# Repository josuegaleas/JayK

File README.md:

# JayK
Full-size mechanical keyboard with USB-C and no lighting, inspired by the [ONO-SENDAI MATRIX 83](https://imgur.com/a/v5pzh#FiXKcm0).

JayK Pro with *more* features can be found [here](https://github.com/josuegaleas/JayK-Pro).

### Disclaimer
I have not printed this PCB out yet, and I am not 100% certain the design works. Please print with discretion.

## Features
- TMK-based firmware
- Numpad on the left for comfort
- USB-C port for modernness
- No lighting for less complexity and lower cost

## Layout
### Default Layer

### Other Layers

JSON files for these layouts can be found [here](https://gist.github.com/josuegaleas/417a4ff5fc216ecdc7868effc9a7b36f) and [here](https://gist.github.com/josuegaleas/c81fd5085f4eeaf2fcede5950b9f7410), for editing in [KLE](http://www.keyboard-layout-editor.com/).

## Major Components
- Microcontroller — [Microchip's AT90USB1286](https://www.microchip.com/wwwproducts/en/AT90USB1286)
- USB-C Port — [Amphenol's 12401610E4#2A](https://www.amphenol-icc.com/usb-3-1-type-c-gen-2-12401610e42a.html)
- Crystal — [EPSON's FA-238](https://www5.epsondevice.com/en/products/crystal_unit/fa238.html)

## Tools
- Layout — [Keyboard Layout Editor](http://www.keyboard-layout-editor.com/)
- PCB — [KiCad EDA](https://kicad.org/)
- Firmware
	- [tmk_core](https://github.com/tmk/tmk_core)
	- [avr-gcc](https://www.gnu.org/software/gcc/gcc.html)
	- [dfu-programmer](https://dfu-programmer.sourceforge.io/)
- Models — [Plate & Case Builder](http://builder.swillkb.com/)

### KiCad Libraries
- [kicad_lib_tmk](https://github.com/tmk/kicad_lib_tmk)
- [keyboard_parts.pretty](https://github.com/tmk/keyboard_parts.pretty)
- [keebs.pretty](https://github.com/egladman/keebs.pretty)
- [jay-kicad-lib](https://github.com/josuegaleas/jay-kicad-lib)

## Development
Clone this repository with:
```bash
git clone --recursive https://github.com/josuegaleas/JayK.git
```

### Hardware
Within KiCad, navigate to the `PCB` folder and open `JayK.pro`.

Using a grid size of `0.0234375` inches for editing the layout.

### Software
Firmware can be compiled using `make` within the `Firmware` folder.

Refer to [this](https://github.com/tmk/tmk_keyboard/blob/master/tmk_core/doc/build.md) for dependencies and programming.

## References
- Layout — [Physical Keyboard Layouts Explained In Detail](https://drop.com/talk/947/physical-keyboard-layouts-explained-in-detail)
- PCB
	- [Keyboard PCB Guide](https://github.com/ruiqimao/keyboard-pcb-guide)
	- [Teensy++ 2.0 USB Development Board](https://www.pjrc.com/store/teensypp.html)
	- [Microchip's AT90USBKEY](https://www.microchip.com/DevelopmentTools/ProductDetails/AT90USBKEY2)
- Firmware
	- [TMK Keyboard Firmware Collection](https://github.com/tmk/tmk_keyboard/)
	- [How to build your very own keyboard firmware](https://deskthority.net/viewtopic.php?f=7&t=7177&start=)

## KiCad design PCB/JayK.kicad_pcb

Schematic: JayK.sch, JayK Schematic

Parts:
C_AREF1: 100n; C_0805_2012Metric_Pad1.15x1.40mm_HandSolder
C_AVCC1: 100n; C_0805_2012Metric_Pad1.15x1.40mm_HandSolder
C_CLK1, C_CLK2: 22p; C_0805_2012Metric_Pad1.15x1.40mm_HandSolder
C_UCAP1: 1u; C_0805_2012Metric_Pad1.15x1.40mm_HandSolder
C_UVCC1: 100n; C_0805_2012Metric_Pad1.15x1.40mm_HandSolder
C_VBUS1: 10u; C_0805_2012Metric_Pad1.15x1.40mm_HandSolder
C_VCC1, C_VCC2: 100n; C_0805_2012Metric_Pad1.15x1.40mm_HandSolder
R_HWB1: 1k; R_0805_2012Metric_Pad1.15x1.40mm_HandSolder
R_RST1: 47k; R_0805_2012Metric_Pad1.15x1.40mm_HandSolder
R_USB1, R_USB2: 22; R_0805_2012Metric_Pad1.15x1.40mm_HandSolder
SW1: SW_PUSH; SW_SPST_TL3342
U1: AT90USB1286-AU; TQFP-64_14x14mm_P0.8mm
Y1: 16M; Crystal_SMD_SeikoEpson_FA238-4Pin_3.2x2.5mm_HandSoldering

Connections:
/CLK_N: C_CLK2.1, U1.24, Y1.3
/CLK_P: C_CLK1.1, U1.23, Y1.1
/D_+: R_USB2.1, U1.5
/D_-: R_USB1.1, U1.4
/D_N: R_USB1.2; also elsewhere on the board
/D_P: R_USB2.2; also elsewhere on the board
/col00: U1.28; also elsewhere on the board
/col01: U1.29; also elsewhere on the board
/col02: U1.30; also elsewhere on the board
/col03: U1.31; also elsewhere on the board
/col04: U1.32; also elsewhere on the board
/col05: U1.35; also elsewhere on the board
/col06: U1.36; also elsewhere on the board
/col07: U1.37; also elsewhere on the board
/col08: U1.38; also elsewhere on the board
/col09: U1.39; also elsewhere on the board
/col10: U1.40; also elsewhere on the board
/col11: U1.41; also elsewhere on the board
/col12: U1.42; also elsewhere on the board
/col13: U1.54; also elsewhere on the board
/col14: U1.55; also elsewhere on the board
/col15: U1.56; also elsewhere on the board
/col16: U1.57; also elsewhere on the board
/col17: U1.58; also elsewhere on the board
/col18: U1.59; also elsewhere on the board
/col19: U1.60; also elsewhere on the board
/col20: U1.61; also elsewhere on the board
/row0: U1.48; also elsewhere on the board
/row1: U1.47; also elsewhere on the board
/row2: U1.46; also elsewhere on the board
/row3: U1.45; also elsewhere on the board
/row4: U1.44; also elsewhere on the board
GND: C_AREF1.2, C_AVCC1.2, C_CLK1.2, C_CLK2.2, C_UCAP1.2, C_UVCC1.2, C_VBUS1.2, C_VCC1.2, C_VCC2.2, R_HWB1.1, SW1.1, U1.6, U1.22, U1.53, U1.63, Y1.2, Y1.4; also elsewhere on the board
unnamed: C_AREF1.1, U1.62
unnamed: C_UCAP1.1, U1.7
unnamed: R_HWB1.2, U1.43
unnamed: R_RST1.1, SW1.2, U1.20
VCC: C_AVCC1.1, C_UVCC1.1, C_VBUS1.1, C_VCC1.1, C_VCC2.1, R_RST1.2, U1.3, U1.8, U1.21, U1.52, U1.64; also elsewhere on the board

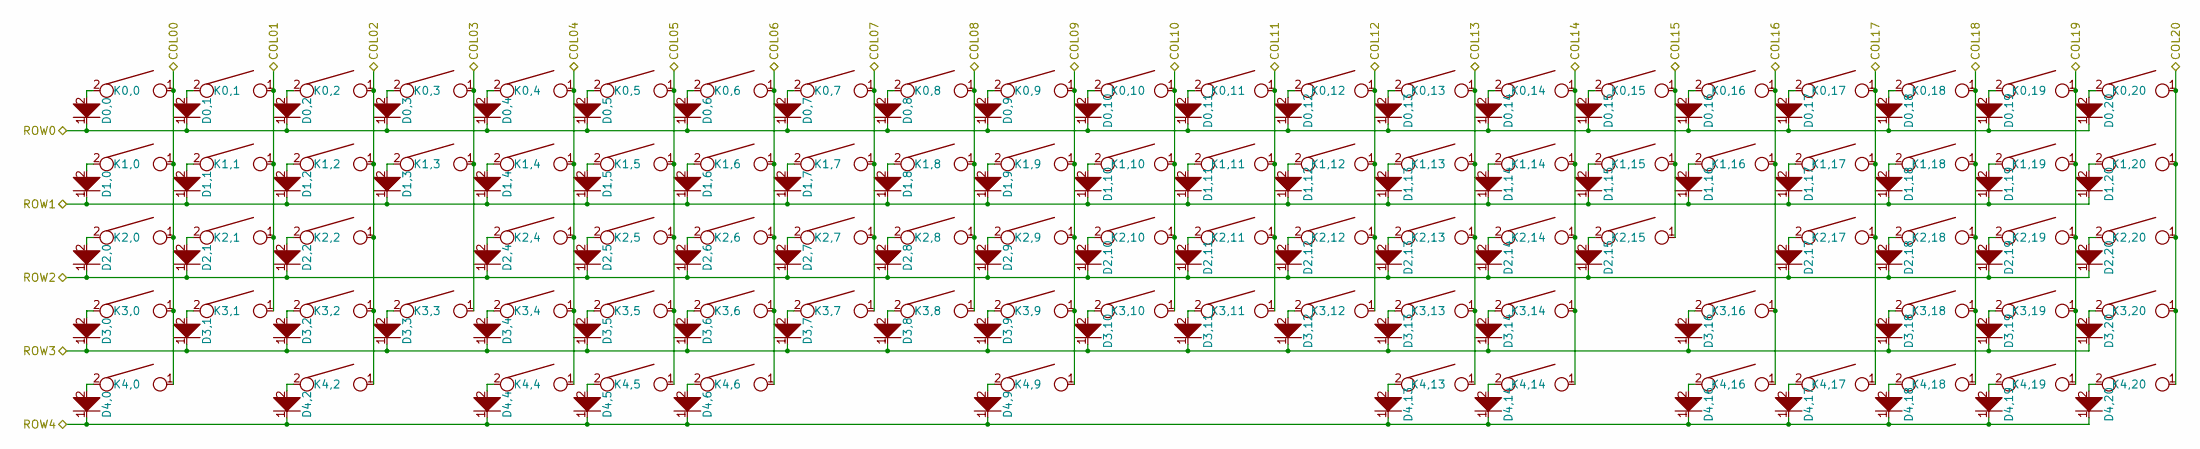
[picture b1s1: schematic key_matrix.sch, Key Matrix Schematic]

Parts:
D0,0, D0,1, D0,2, D0,3, D0,4, D0,5, D0,6, D0,7, D0,8, D0,9, D0,10, D0,11, D0,12, D0,13, D0,14, D0,15, D0,16, D0,17, D0,18, D0,19, D0,20, D1,0, D1,1, D1,2, D1,3, D1,4, D1,5, D1,6, D1,7, D1,8, D1,9, D1,10, D1,11, D1,12, D1,13, D1,14, D1,15, D1,16, D1,17, D1,18, D1,19, D1,20, D2,0, D2,1, D2,2, D2,4, D2,5, D2,6, D2,7, D2,8, D2,9, D2,10, D2,11, D2,12, D2,13, D2,14, D2,15, D2,17, D2,18, D2,19, D2,20, D3,0, D3,1, D3,2, D3,3, D3,4, D3,5, D3,6, D3,7, D3,8, D3,9, D3,10, D3,11, D3,12, D3,13, D3,14, D3,16, D3,18, D3,19, D3,20, D4,0, D4,2, D4,4, D4,5, D4,6, D4,9, D4,13, D4,14, D4,16, D4,17, D4,18, D4,19, D4,20: D; D_SOD123_axial
K0,0, K0,1, K0,2, K0,3, K0,4, K0,5, K0,6, K0,7, K0,8, K0,9, K0,10, K0,11, K0,12, K0,13, K0,14, K0,15, K0,16, K0,18, K0,19, K0,20, K1,0, K1,1, K1,2, K1,5, K1,6, K1,7, K1,8, K1,9, K1,10, K1,11, K1,12, K1,13, K1,14, K1,15, K1,16, K1,18, K1,19, K1,20, K2,0, K2,1, K2,2, K2,5, K2,6, K2,7, K2,8, K2,9, K2,10, K2,11, K2,12, K2,13, K2,14, K2,15, K2,18, K2,19, K2,20, K3,0, K3,1, K3,2, K3,5, K3,6, K3,7, K3,8, K3,9, K3,10, K3,11, K3,12, K3,13, K3,14, K3,18, K3,19, K3,20, K4,2, K4,18, K4,19, K4,20: KEYSW; Mx_Alps_100
K0,17, K1,3, K3,3, K4,0: KEYSW; Mx_Alps_200
K1,4, K1,17: KEYSW; Mx_Alps_150
K2,4: KEYSW; Mx_Alps_175
K2,17, K3,4: KEYSW; Mx_Alps_225
K3,16: KEYSW; Mx_Alps_275
K4,4, K4,5, K4,6, K4,13, K4,14, K4,16, K4,17: KEYSW; Mx_Alps_125
K4,9: KEYSW; Mx_Alps_625

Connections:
/col00: K0,0.1, K1,0.1, K2,0.1, K3,0.1, K4,0.1; also elsewhere on the board
/col01: K0,1.1, K1,1.1, K2,1.1, K3,1.1; also elsewhere on the board
/col02: K0,2.1, K1,2.1, K2,2.1, K3,2.1, K4,2.1; also elsewhere on the board
/col03: K0,3.1, K1,3.1, K3,3.1; also elsewhere on the board
/col04: K0,4.1, K1,4.1, K2,4.1, K3,4.1, K4,4.1; also elsewhere on the board
/col05: K0,5.1, K1,5.1, K2,5.1, K3,5.1, K4,5.1; also elsewhere on the board
/col06: K0,6.1, K1,6.1, K2,6.1, K3,6.1, K4,6.1; also elsewhere on the board
/col07: K0,7.1, K1,7.1, K2,7.1, K3,7.1; also elsewhere on the board
/col08: K0,8.1, K1,8.1, K2,8.1, K3,8.1; also elsewhere on the board
/col09: K0,9.1, K1,9.1, K2,9.1, K3,9.1, K4,9.1; also elsewhere on the board
/col10: K0,10.1, K1,10.1, K2,10.1, K3,10.1; also elsewhere on the board
/col11: K0,11.1, K1,11.1, K2,11.1, K3,11.1; also elsewhere on the board
/col12: K0,12.1, K1,12.1, K2,12.1, K3,12.1; also elsewhere on the board
/col13: K0,13.1, K1,13.1, K2,13.1, K3,13.1, K4,13.1; also elsewhere on the board
/col14: K0,14.1, K1,14.1, K2,14.1, K3,14.1, K4,14.1; also elsewhere on the board
/col15: K0,15.1, K1,15.1, K2,15.1; also elsewhere on the board
/col16: K0,16.1, K1,16.1, K3,16.1, K4,16.1; also elsewhere on the board
/col17: K0,17.1, K1,17.1, K2,17.1, K4,17.1; also elsewhere on the board
/col18: K0,18.1, K1,18.1, K2,18.1, K3,18.1, K4,18.1; also elsewhere on the board
/col19: K0,19.1, K1,19.1, K2,19.1, K3,19.1, K4,19.1; also elsewhere on the board
/col20: K0,20.1, K1,20.1, K2,20.1, K3,20.1, K4,20.1; also elsewhere on the board
/row0: D0,0.1, D0,1.1, D0,2.1, D0,3.1, D0,4.1, D0,5.1, D0,6.1, D0,7.1, D0,8.1, D0,9.1, D0,10.1, D0,11.1, D0,12.1, D0,13.1, D0,14.1, D0,15.1, D0,16.1, D0,17.1, D0,18.1, D0,19.1, D0,20.1; also elsewhere on the board
/row1: D1,0.1, D1,1.1, D1,2.1, D1,3.1, D1,4.1, D1,5.1, D1,6.1, D1,7.1, D1,8.1, D1,9.1, D1,10.1, D1,11.1, D1,12.1, D1,13.1, D1,14.1, D1,15.1, D1,16.1, D1,17.1, D1,18.1, D1,19.1, D1,20.1; also elsewhere on the board
/row2: D2,0.1, D2,1.1, D2,2.1, D2,4.1, D2,5.1, D2,6.1, D2,7.1, D2,8.1, D2,9.1, D2,10.1, D2,11.1, D2,12.1, D2,13.1, D2,14.1, D2,15.1, D2,17.1, D2,18.1, D2,19.1, D2,20.1; also elsewhere on the board
/row3: D3,0.1, D3,1.1, D3,2.1, D3,3.1, D3,4.1, D3,5.1, D3,6.1, D3,7.1, D3,8.1, D3,9.1, D3,10.1, D3,11.1, D3,12.1, D3,13.1, D3,14.1, D3,16.1, D3,18.1, D3,19.1, D3,20.1; also elsewhere on the board
/row4: D4,0.1, D4,2.1, D4,4.1, D4,5.1, D4,6.1, D4,9.1, D4,13.1, D4,14.1, D4,16.1, D4,17.1, D4,18.1, D4,19.1, D4,20.1; also elsewhere on the board
unnamed: D0,0.2, K0,0.2
unnamed: D0,1.2, K0,1.2
unnamed: D0,2.2, K0,2.2
unnamed: D0,3.2, K0,3.2
unnamed: D0,4.2, K0,4.2
unnamed: D0,5.2, K0,5.2
unnamed: D0,6.2, K0,6.2
unnamed: D0,7.2, K0,7.2
unnamed: D0,8.2, K0,8.2
unnamed: D0,9.2, K0,9.2
unnamed: D0,10.2, K0,10.2
unnamed: D0,11.2, K0,11.2
unnamed: D0,12.2, K0,12.2
unnamed: D0,13.2, K0,13.2
unnamed: D0,14.2, K0,14.2
unnamed: D0,15.2, K0,15.2
unnamed: D0,16.2, K0,16.2
unnamed: D0,17.2, K0,17.2
unnamed: D0,18.2, K0,18.2
unnamed: D0,19.2, K0,19.2
unnamed: D0,20.2, K0,20.2
unnamed: D1,0.2, K1,0.2
unnamed: D1,1.2, K1,1.2
unnamed: D1,2.2, K1,2.2
unnamed: D1,3.2, K1,3.2
unnamed: D1,4.2, K1,4.2
unnamed: D1,5.2, K1,5.2
unnamed: D1,6.2, K1,6.2
unnamed: D1,7.2, K1,7.2
unnamed: D1,8.2, K1,8.2
unnamed: D1,9.2, K1,9.2
unnamed: D1,10.2, K1,10.2
unnamed: D1,11.2, K1,11.2
unnamed: D1,12.2, K1,12.2
unnamed: D1,13.2, K1,13.2
unnamed: D1,14.2, K1,14.2
unnamed: D1,15.2, K1,15.2
unnamed: D1,16.2, K1,16.2
unnamed: D1,17.2, K1,17.2
unnamed: D1,18.2, K1,18.2
unnamed: D1,19.2, K1,19.2
unnamed: D1,20.2, K1,20.2
unnamed: D2,0.2, K2,0.2
unnamed: D2,1.2, K2,1.2
unnamed: D2,2.2, K2,2.2
unnamed: D2,4.2, K2,4.2
unnamed: D2,5.2, K2,5.2
unnamed: D2,6.2, K2,6.2
unnamed: D2,7.2, K2,7.2
unnamed: D2,8.2, K2,8.2
unnamed: D2,9.2, K2,9.2
unnamed: D2,10.2, K2,10.2
unnamed: D2,11.2, K2,11.2
unnamed: D2,12.2, K2,12.2
unnamed: D2,13.2, K2,13.2
unnamed: D2,14.2, K2,14.2
unnamed: D2,15.2, K2,15.2
unnamed: D2,17.2, K2,17.2
unnamed: D2,18.2, K2,18.2
unnamed: D2,19.2, K2,19.2
unnamed: D2,20.2, K2,20.2
unnamed: D3,0.2, K3,0.2
unnamed: D3,1.2, K3,1.2
unnamed: D3,2.2, K3,2.2
unnamed: D3,3.2, K3,3.2
unnamed: D3,4.2, K3,4.2
unnamed: D3,5.2, K3,5.2
unnamed: D3,6.2, K3,6.2
unnamed: D3,7.2, K3,7.2
unnamed: D3,8.2, K3,8.2
unnamed: D3,9.2, K3,9.2
unnamed: D3,10.2, K3,10.2
unnamed: D3,11.2, K3,11.2
unnamed: D3,12.2, K3,12.2
unnamed: D3,13.2, K3,13.2
unnamed: D3,14.2, K3,14.2
unnamed: D3,16.2, K3,16.2
unnamed: D3,18.2, K3,18.2
unnamed: D3,19.2, K3,19.2
unnamed: D3,20.2, K3,20.2
unnamed: D4,0.2, K4,0.2
unnamed: D4,2.2, K4,2.2
unnamed: D4,4.2, K4,4.2
unnamed: D4,5.2, K4,5.2
unnamed: D4,6.2, K4,6.2
unnamed: D4,9.2, K4,9.2
unnamed: D4,13.2, K4,13.2
unnamed: D4,14.2, K4,14.2
unnamed: D4,16.2, K4,16.2
unnamed: D4,17.2, K4,17.2
unnamed: D4,18.2, K4,18.2
unnamed: D4,19.2, K4,19.2
unnamed: D4,20.2, K4,20.2

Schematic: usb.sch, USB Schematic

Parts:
D_ESD1: PESD5V0L2BT; SOT-23_Handsoldering
D_VBUS1: D; D_SOD123_axial
J1: USB_C_Receptacle_USB2.0; USB_C_Receptacle_Amphenol_12401610E4-2A
R_USB3, R_USB4: 5.1k; R_0805_2012Metric_Pad1.15x1.40mm_HandSolder

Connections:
/D_N: D_ESD1.1, J1.A7, J1.B7; also elsewhere on the board
/D_P: D_ESD1.2, J1.A6, J1.B6; also elsewhere on the board
GND: D_ESD1.3, J1.A1, J1.A12, J1.B1, J1.B12, J1.S1, R_USB3.2, R_USB4.2; also elsewhere on the board
unnamed: D_VBUS1.2, J1.A4, J1.A9, J1.B4, J1.B9
unnamed: J1.A5, R_USB3.1
unnamed: J1.B5, R_USB4.1
VCC: D_VBUS1.1; also elsewhere on the board

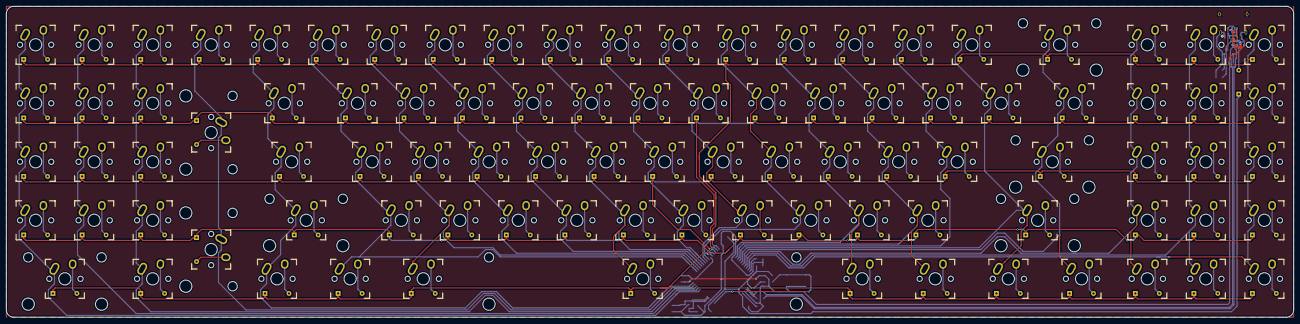
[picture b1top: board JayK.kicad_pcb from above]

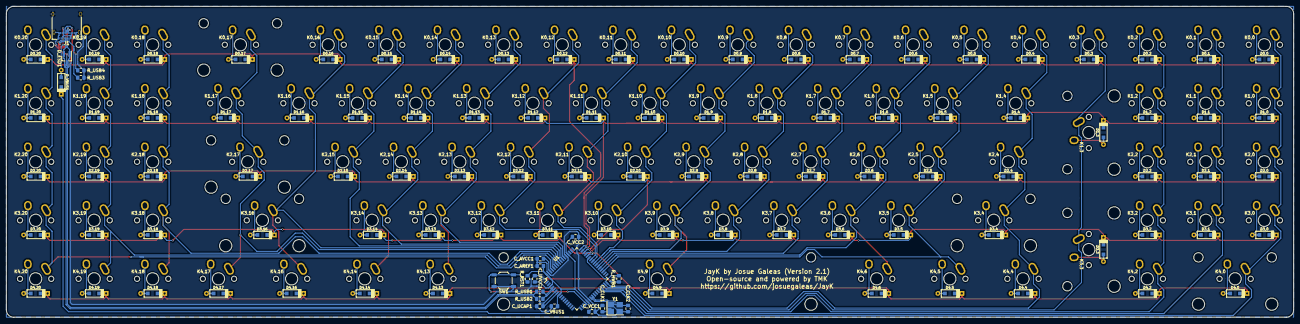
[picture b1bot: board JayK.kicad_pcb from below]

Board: 2 copper layers, 419.1 x 101.2 mm, 207 parts (114 on the bottom side), 134 nets.

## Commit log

2017-01-30 Setting up libraries and working environments
2017-02-11 In process of moving submodules elsewhere
2017-02-11 Added basic switch layout
2017-02-12 Oriented diodes; laid down MCU and BT module
2017-02-14 Switched MCUs; removed BT for now
2017-02-18 USB routed and most components connected
2017-02-20 Connected columns and rows
2017-02-23 Additional routing: col1 and col2 connected
2017-02-28 Trying a new MCU orientation to make room routes
2017-02-28 Reached a roadblock with this orientation
2017-03-01 Rotated MCU; rerouting
2017-03-02 Connected many columns
2017-03-03 All rows and columns connected
2017-03-10 Started cleanup of routes and vias
2017-03-10 Updated readme with more references; set up firmware libs
2017-03-17 Updated README with more info
2017-03-22 Added layout; updated README with an image
2017-03-22 More routing cleanup
2017-05-17 Redid the layout to resemble the Teensy++ 2.0 more
2017-05-20 Updating libraries and gitignore
2017-08-07 Removed unused footprint library; taking new design approach
2017-08-07 Taking new design approach; updated submodules
2017-08-07 Updated README; updated layout
2017-11-08 2017.11.08 Update
2017-11-10 2017.11.10 Update
    - Updated README with more information
    - Updated layout slightly
    - Added a KiCad library for MCU
2017-11-12 2017.11.11 Nightly
2017-11-14 2017.11.14 Nightly
2017-11-14 2017.11.14 Update
    - Redid schematic and layout
    - Now using USB-C connector
2017-11-16 2017.11.15 Update
    - Layed out most electronics on the board
2017-12-19 2017.12.19 Update
2018-01-22 2018.01.22 Update
    - Most of the routing done for the new setup
2018-01-24 2018.01.24 Update
    - Almost all routing complete
    - Only Vcc lines remain to connect
2018-01-24 2018.01.24 Update 2
    - Vcc line now routed
    - Further cleanup is needed
2018-01-25 2018.01.25 Update
    - Routing should be complete
    - Did more cleanup, GND lines/pins connected
2018-03-03 2018.03.3 Update
    - Moved layout image to another repository
    - Removed JSON file and added direct link to gist
    - Added feature list to the README
2018-03-15 2018.03.15 Nightly
2018-03-16 2018.03.15 Update
    - Updated labels on switches and diodes to better match array subscripts
    - Started preliminary C code for the firmware
2018-03-17 2018.03.16 Update
    - Created makefile
    - Added macro for handling keyboard layouts
2018-03-19 2018.03.19 Update
    - Added led.c, necessary for compilation
    - Wrote matrix.c, however currently does not work
    - Updated README
    - Updated components list
    - Added firmware tools
    - Added new reference
2018-03-20 2018.03.20 Update
    - Fixed shift count overflow
    - Removed unnecessary comments
2018-03-28 2018.03.27 Update
    - Updated gitignore for KiCad files and C files
    - Renamed Models folder to Case
    - Deleted cache file
    - Updated readme with link to JayKey2
2018-03-31 2018.03.30 Update
    - Updated readme to have an image of the different layers
2018-04-16 2018.04.16 Nightly
2018-04-20 2018.04.20 Update
    - Official version 1.0 release
    - Cleaned up routing on PCB and moved components for a cleaner design
    - Made new constant in matrix.c called 'one' which makes read_cols function easier to read
2018-04-24 2018.04.24 Update
    - Updated Doragasu's library
2018-04-28 2018.04.27 Update
    - Version 1.1 Release
    - Cleaned up routing to the USB port
    - Made seperate schematic sheet with key matrix (so it can be used in JayKey2)
2018-07-17 2018.07.17 Update
    - Updated readme with disclaimer and planned features
2018-07-29 2018.07.29 Nightly
2018-08-27 2018.08.27 Nightly
2018-08-28 2018.08.28 Nightly
2018-09-23 2018.09.23 Nightly
2018-09-23 2018.09.23 Nightly 2
2018-09-24 2018.09.23 Nightly 3
2018-09-25 2018.09.25 Nightly
2018-09-29 2018.09.29 Nightly
2018-10-02 2018.10.02 Nightly
2018-10-12 2018.10.11 Nightly
2018-10-25 2018.10.25 Nightly
2018-11-29 2018.11.29 Nightly
2018-12-04 2018.12.04 Nightly
2018-12-06 2018.12.06 Nightly
2018-12-14 2018.12.14 Nightly
2018-12-15 2018.12.14 Nightly 2
2018-12-15 2018.12.14 Update
    - Moved project to KiCad 5.0
    - Using my own KiCad library instead of doragasu's library
    - Re-did all the tracing; much cleaner design now
    - Moved components around to be more correctly placed
    - Updated footprints in accordance to 5.0's libraries
    - USB data lines and clock lines were made differential pairs for correctness
2019-11-13 2019.11.13 Update
    - Renamed from JayKey1 to JayK
    - Officially opened on KiCad 5.1 and known to be working
    - Added missing power flag on VBUS line from USB port
    - Fixed courtyard overlaps in layout
    - Added the apparently missing ground plane on the front side
    - Fixed issue #1
2021-11-10 2021.11.09 Update
    - Updated link to KiCad's website, nothing else
    - More info here: https://forum.kicad.info/t/warning-avoid-all-links-to-kicad-pcb-org-use-kicad-org/31521
